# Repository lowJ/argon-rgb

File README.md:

# argon-rgb

RGB controller board for my PC.
Using Particle Argon

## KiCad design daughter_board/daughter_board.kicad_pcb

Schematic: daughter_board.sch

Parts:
C1, C2: 0.01uF; C_1206_3216Metric_Pad1.33x1.80mm_HandSolder
J1: SJ2-3574A-SMT-TR; CUI_SJ2-35043A-SMT-TR; PARTREV 1.02
R1, R2: 10K; R_1206_3216Metric_Pad1.30x1.75mm_HandSolder
SW1: SW_Push; SW_Cherry_MX_1.00u_PCB
SW2: Rotary_Encoder; RotaryEncoder_Alps_EC11E_Vertical_H20mm

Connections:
GND: C1.2, C2.2, J1.1, SW1.2, SW2.C
unnamed: J1.2, SW1.1
unnamed: R1.1, SW2.A
unnamed: R2.1, SW2.B
OUT_A: C1.1, J1.4, R1.2
OUT_B: C2.1, J1.3, R2.2

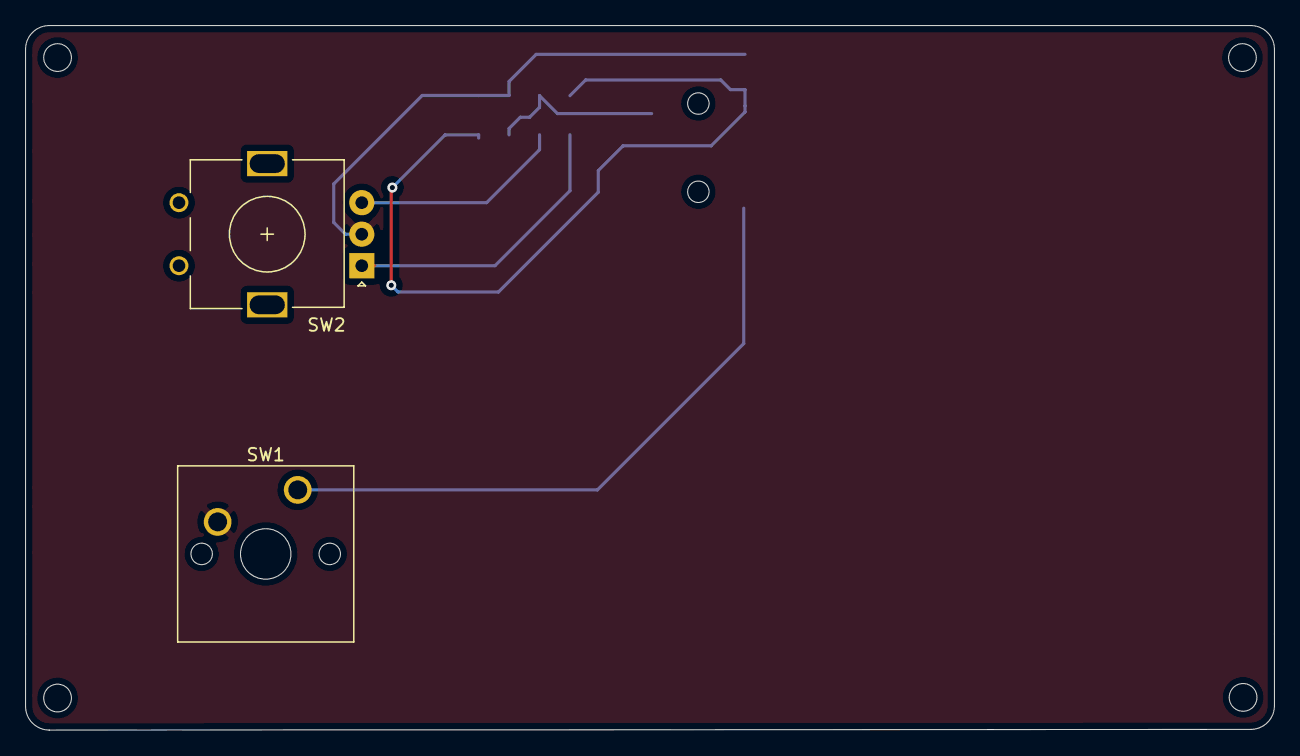
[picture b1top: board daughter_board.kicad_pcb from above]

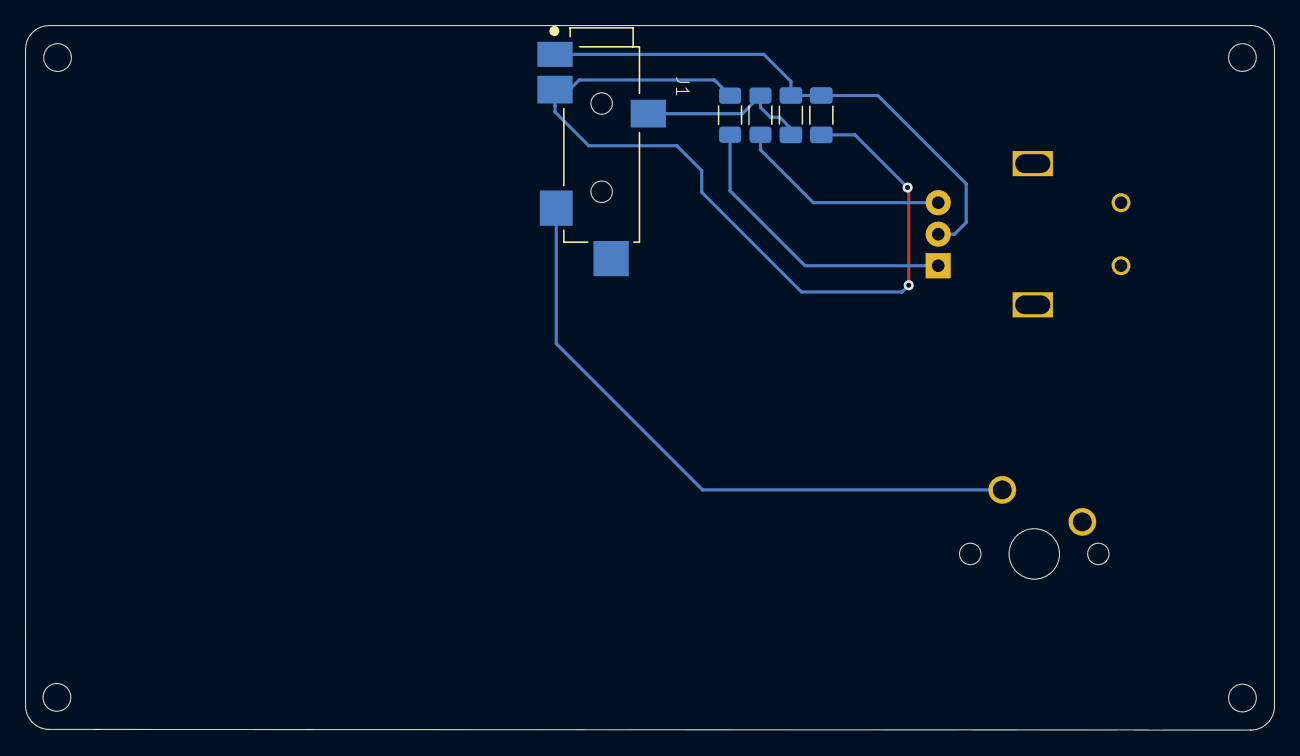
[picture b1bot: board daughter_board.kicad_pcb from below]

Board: 2 copper layers, 99.1 x 55.9 mm, 7 parts (5 on the bottom side), 6 nets.

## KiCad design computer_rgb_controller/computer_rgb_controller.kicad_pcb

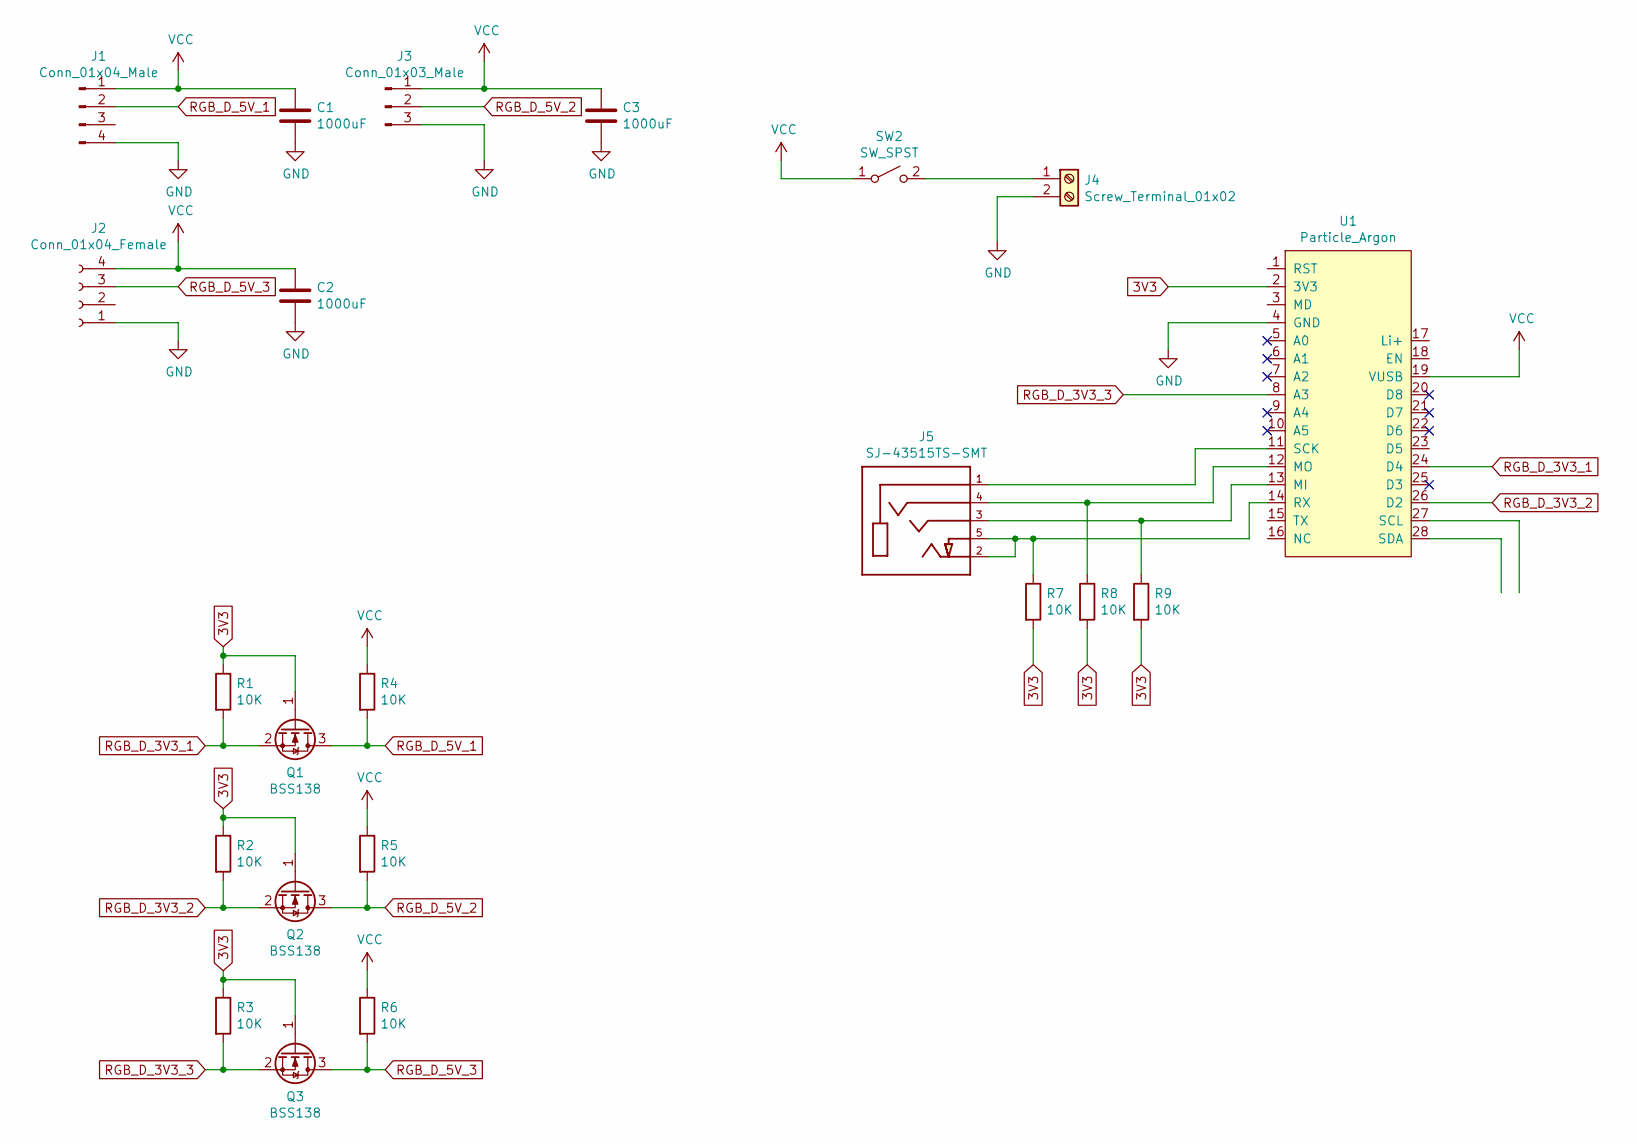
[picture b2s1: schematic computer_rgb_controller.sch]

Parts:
C1, C2, C3: 1000uF; CP_Radial_D10.0mm_P5.00mm
J1: Conn_01x04_Male; PinHeader_1x04_P2.54mm_Vertical
J2: Conn_01x04_Female; PinSocket_1x04_P2.54mm_Vertical
J3: Conn_01x03_Male; PinHeader_1x03_P2.54mm_Vertical
J4: Screw_Terminal_01x02; TerminalBlock_bornier-2_P5.08mm
J5: SJ-43515TS-SMT; CUI_SJ-43515TS-SMT
Q1, Q2, Q3: BSS138; SOT-23
R1, R2, R3, R4, R5, R6, R7, R8, R9: 10K; R_1206_3216Metric_Pad1.30x1.75mm_HandSolder
SW2: SW_SPST; rocker_sw
U1: Particle_Argon

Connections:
3V3: Q1.1 (G), Q2.1 (G), Q3.1 (G), R1.1, R2.1, R3.1, R7.2, R8.2, R9.2, U1.2 (3V3)
GND: C1.2, C2.2, C3.2, J1.4, J2.1, J3.3, J4.2, U1.4 (GND)
unnamed: J4.1, SW2.2 (B)
unnamed: J5.1, U1.11 (SCK)
unnamed: J5.2, J5.5, R7.1, U1.14 (RX)
unnamed: J5.3, R9.1, U1.13 (MI)
unnamed: J5.4, R8.1, U1.12 (MO)
RGB_D_3V3_1: Q1.2 (S), R1.2, U1.24 (D4)
RGB_D_3V3_2: Q2.2 (S), R2.2, U1.26 (D2)
RGB_D_3V3_3: Q3.2 (S), R3.2, U1.8 (A3)
RGB_D_5V_1: J1.2, Q1.3 (D), R4.2
RGB_D_5V_2: J3.2, Q2.3 (D), R5.2
RGB_D_5V_3: J2.3, Q3.3 (D), R6.2
VCC: C1.1, C2.1, C3.1, J1.1, J2.4, J3.1, R4.1, R5.1, R6.1, SW2.1 (A), U1.19 (VUSB)

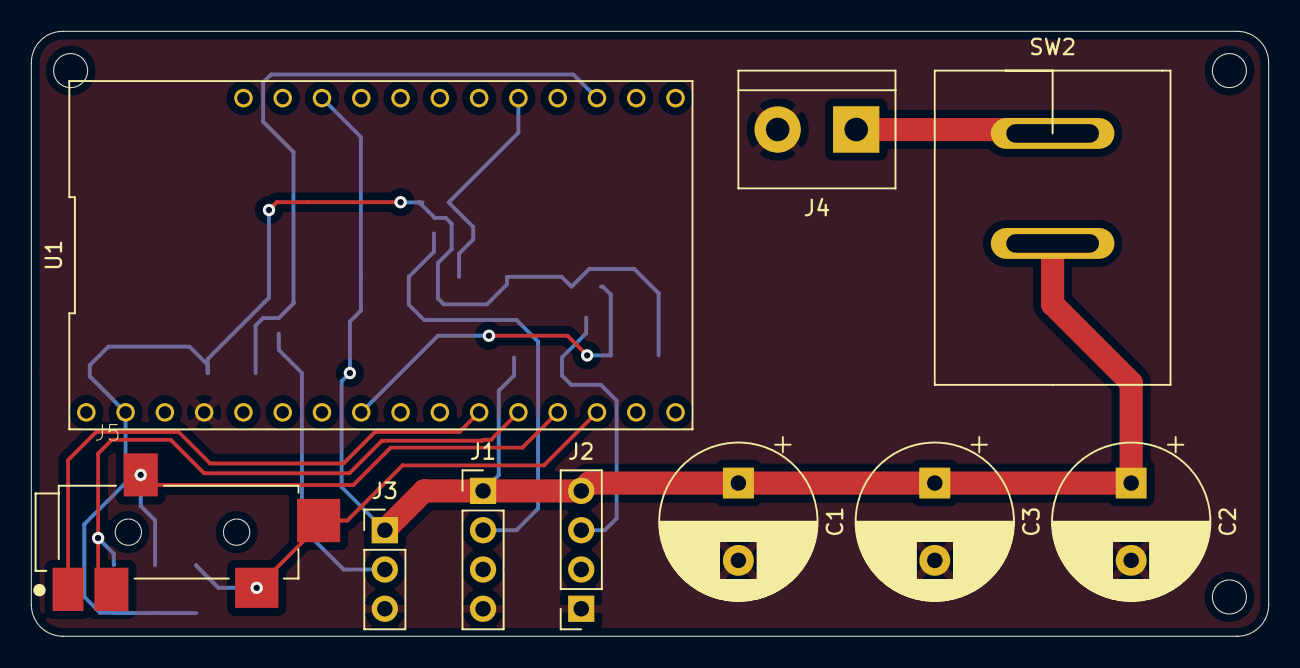
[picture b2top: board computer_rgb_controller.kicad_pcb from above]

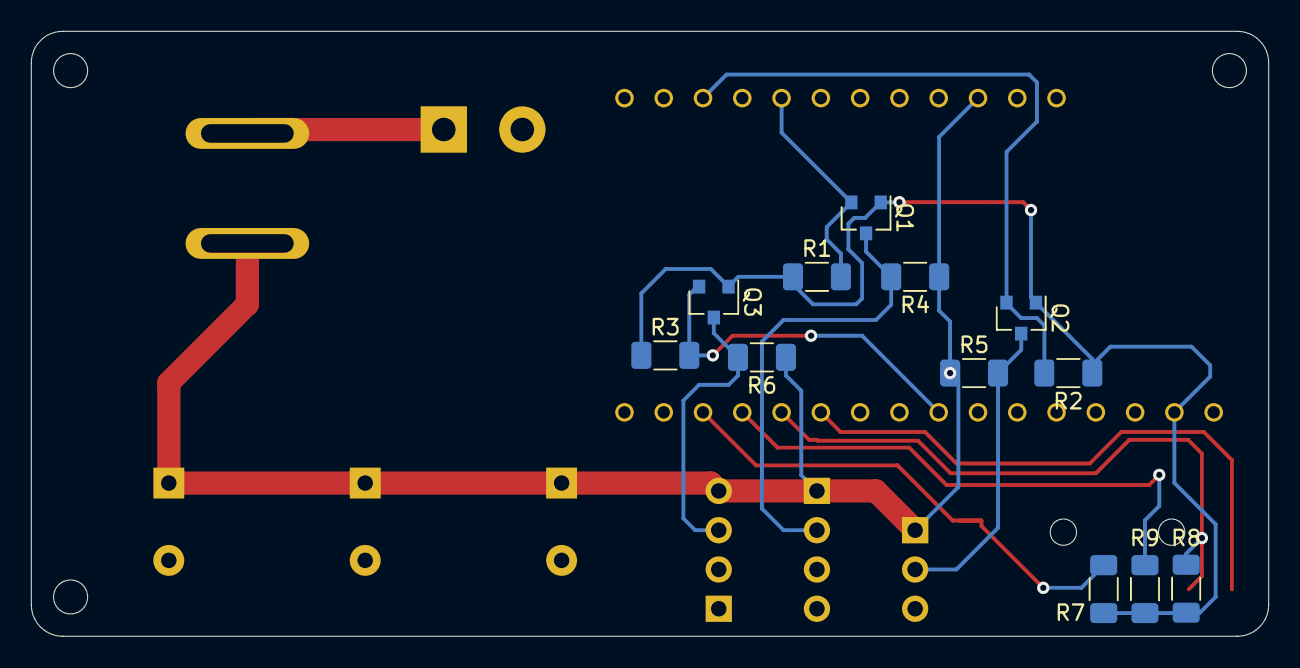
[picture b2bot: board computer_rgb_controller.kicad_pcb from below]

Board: 2 copper layers, 80.0 x 39.1 mm, 22 parts (12 on the bottom side), 14 nets.

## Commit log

2020-10-30 first :000
2020-10-31 added to schematic
2020-11-15 finished main board pcb
2020-11-24 modified connector location to avoid clerance issues
2020-11-26 updated trrs jack, old one was out of stock :(
2021-03-22 updated TRRS jack bc previous one was wrong one
2021-03-22 update daughter board
2021-05-02 generated gerbers sending to manufacturer
